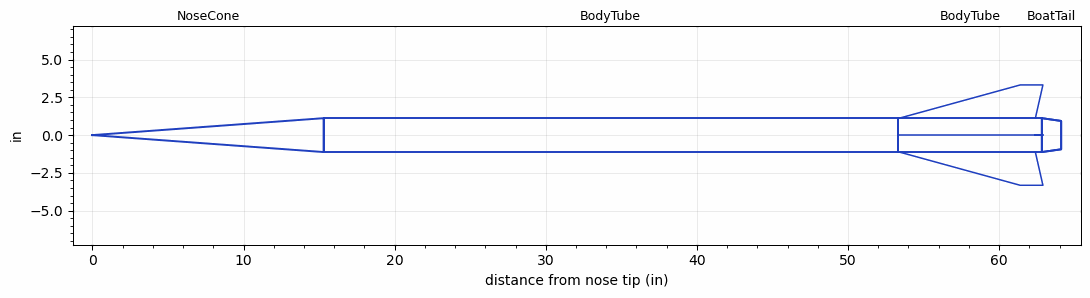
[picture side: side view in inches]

<RASAeroDocument>
 <FileVersion>2</FileVersion>
 <RocketDesign>
  <NoseCone>
   <Length>15.3</Length>
   <Diameter>2.242</Diameter>
   <Shape>Conical</Shape>
   <BluntRadius>0.05</BluntRadius>
   <Location>0</Location>
  </NoseCone>
  <BodyTube>
   <Length>38</Length>
   <Diameter>2.242</Diameter>
   <Location>15.3</Location>
  </BodyTube>
  <BodyTube>
   <Length>9.53</Length>
   <Diameter>2.242</Diameter>
   <Location>53.3</Location>
   <BoattailLength>1.277</BoattailLength>
   <BoattailRearDiameter>1.876</BoattailRearDiameter>
   <Fin>
    <Count>4</Count>
    <Chord>9</Chord>
    <Span>2.2</Span>
    <SweepDistance>8</SweepDistance>
    <TipChord>1.5</TipChord>
    <Thickness>0.125</Thickness>
    <LERadius>0.03</LERadius>
    <Location>9.43</Location>
    <AirfoilSection>Hexagonal</AirfoilSection>
    <FX1>1.33</FX1>
    <FX3>0.34</FX3>
   </Fin>
  </BodyTube>
  <BoatTail>
   <Length>1.277</Length>
   <Diameter>2.242</Diameter>
   <RearDiameter>1.876</RearDiameter>
   <Location>62.83</Location>
  </BoatTail>
  <Surface>Smooth Paint</Surface>
  <ModifiedBarrowman>True</ModifiedBarrowman>
  <Turbulence>True</Turbulence>
  <UseBooster1>False</UseBooster1>
  <UseBooster2>False</UseBooster2>
 </RocketDesign>
 <LaunchSite>
  <Altitude>4000</Altitude>
  <Pressure>25.85</Pressure>
  <RodAngle>2</RodAngle>
  <RodLength>96</RodLength>
  <Temperature>70</Temperature>
  <WindSpeed>4.47</WindSpeed>
 </LaunchSite>
 <Recovery>
  <Altitude1>0</Altitude1>
  <Altitude2>0</Altitude2>
  <DeviceType1>None</DeviceType1>
  <DeviceType2>None</DeviceType2>
  <Event1>False</Event1>
  <Event2>False</Event2>
  <Size1>0</Size1>
  <Size2>0</Size2>
  <EventType1>None</EventType1>
  <EventType2>None</EventType2>
  <CD1>0</CD1>
  <CD2>0</CD2>
 </Recovery>
 <SimulationList>
  <Simulation>
   <SustainerEngine>M1378LR  (Loki)</SustainerEngine>
   <SustainerLaunchWt>12.7</SustainerLaunchWt>
   <SustainerNozzleDiameter>1.58</SustainerNozzleDiameter>
   <SustainerCG>42.57</SustainerCG>
   <SustainerIgnitionDelay>0</SustainerIgnitionDelay>
   <Booster1SeparationDelay>0</Booster1SeparationDelay>
   <Booster1IgnitionDelay>0</Booster1IgnitionDelay>
   <IncludeBooster1>False</IncludeBooster1>
   <Booster2Delay>0</Booster2Delay>
   <IncludeBooster2>False</IncludeBooster2>
   <TimetoApogee>57.11642</TimetoApogee>
   <MaxAltitude>66618.91</MaxAltitude>
   <MaxVelocity>3474.444</MaxVelocity>
   <OptimumWt>10.26471</OptimumWt>
   <OptimumMaxAlt>10.26471</OptimumMaxAlt>
  </Simulation>
  <Simulation>
   <SustainerLaunchWt>5.9306</SustainerLaunchWt>
   <SustainerCG>45.2677</SustainerCG>
   <SustainerIgnitionDelay>0</SustainerIgnitionDelay>
   <Booster1SeparationDelay>0</Booster1SeparationDelay>
   <Booster1IgnitionDelay>0</Booster1IgnitionDelay>
   <IncludeBooster1>False</IncludeBooster1>
   <Booster2Delay>0</Booster2Delay>
   <IncludeBooster2>False</IncludeBooster2>
  </Simulation>
 </SimulationList>
</RASAeroDocument>
